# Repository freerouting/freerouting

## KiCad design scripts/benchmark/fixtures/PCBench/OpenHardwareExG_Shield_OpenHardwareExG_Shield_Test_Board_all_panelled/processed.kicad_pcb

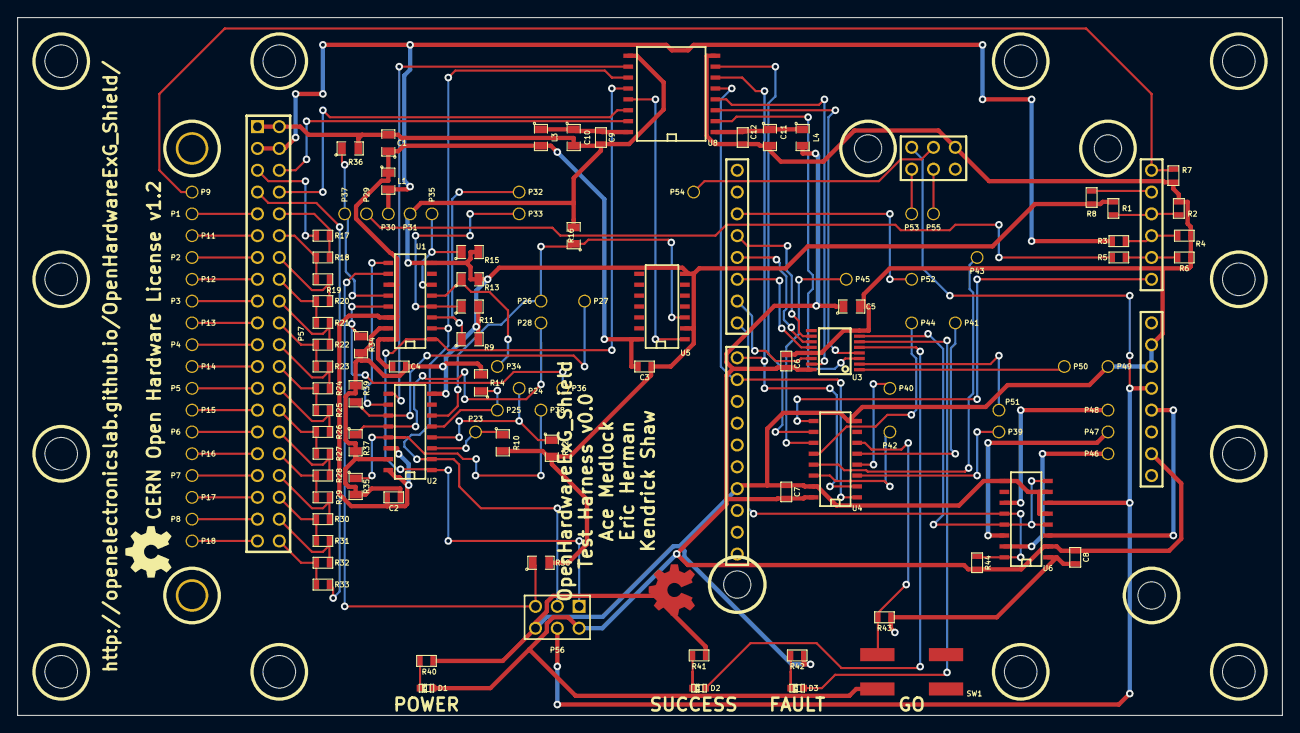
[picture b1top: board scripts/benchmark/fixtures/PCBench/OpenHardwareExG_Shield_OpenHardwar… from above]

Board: 4 copper layers, 147.3 x 81.3 mm, 137 parts (0 on the bottom side), 105 nets.

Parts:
C1, C5, C10, C11: 10uF; SM0805
C2, C3, C4, C6, C7, C8, C9, C12: 100nF; SM0603
D1, D2, D3: LED; LED-0603
Hole_M3, Hole_M3_2, Hole_M3_3, Hole_M3_4, Hole_M3_5, Hole_M3_6, Hole_M3_7, Hole_M3_8, Hole_M3_9, Hole_M3_10, Hole_M3_11, Hole_M3_12, Hole_M3_13, Hole_M3_14: VAL**; Hole_M3
L1, L3, L4: MH2029-221Y; SM0805
P1, P2, P3, P4, P5, P6, P7, P8, P9, P11, P12, P13, P14, P15, P16, P17, P18, P23, P24, P25, P26, P27, P28, P29, P30, P31, P32, P33, P34, P35, P36, P37, P38, P39, P40, P41, P42, P43, P44, P45, P46, P47, P48, P49, P50, P51, P52, P53, P54, P55: CONN_1; POGO_PIN_BASE
P19: ARDUINO_SHIELD; arduino_shield_with_holes
P56: CONN_3X2; pin_array_3x2
P57: CONN_20X2; PIN_ARRAY_20X2
R1, R3, R5, R43, R44: 10k; SM0603
R2, R4, R6: 1k; SM0603
R7: 5.1K; SM0603
R8, R18, R19, R20, R21, R22, R23, R24, R25, R26, R27, R28, R29, R30, R31, R32: 100; SM0603
R9, R10, R11, R12, R13, R14, R15, R16, R34, R35, R36, R37, R38, R39: 1M; SM0805
R17, R33: 15k; SM0603
R40, R41, R42: 560; SM0603
SW1: SW_PUSH; smt-tactile-button
U1, U2, U4: 74HC165; SO16E
U3: 74HC595PWR; TSSOP16
U5: 74LS125; SO14E
U6: TPS2095D; SO16E
U8: SI8661; SO16W

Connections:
+3.3V: P19.93, U6.3
+5V: P19.88, P19.94, P56.4, U6.6
/3.3V_BOGUS_ISO: L1.2, P30.1, P57.3, P57.4, R3.1
/3.3V_BOGUS_ISO_DATA: C9.1, C10.1, L3.1, U8.16
/A1: P19.55, R5.2, R6.1
/A2: P19.56, R3.2, R4.1
/A3: P19.57, R1.2, R2.1
/A4: P19.58, R8.2
/ADS129x_CLK_BOGUS_ISO: P38.1, R35.1, U2.13
/ADS129x_DAISY_IN_BOGUS_ISO: P36.1, R34.1, U1.13
/ADS129x_DOUT: P44.1, U4.12
/ADS129x_DOUT_BOGUS_ISO: P27.1, R39.1, U2.11
/ADS129x_GPIO1_BOGUS_ISO: P32.1, R9.1, U1.3
/ADS129x_GPIO2_BOGUS_ISO: P33.1, R11.1, U1.4
/ADS129x_GPIO3_BOGUS_ISO: P34.1, R13.1, U1.5
/ADS129x_GPIO4_BOGUS_ISO: P35.1, R15.1, U1.6
/ADS129x_MOSI_BOGUS_ISO: P23.1, R10.1, U2.3
/ADS129x_SCLK_BOGUS_ISO: P24.1, R12.1, U2.4
/ADS129x_~CS~: P42.1, U4.14
/ADS129x_~CS~_BOGUS_ISO: P25.1, R14.1, U2.5
/ADS129x_~DRDY~: P45.1, U4.11
/ADS129x_~DRDY~_BOGUS_ISO: P28.1, R37.1, U2.12
/ARDUINO_VCC: C5.1, C6.1, C7.1, C8.1, D1.1, L4.2, P19.91, P56.2, R44.2, SW1.2, U3.16, U4.16, U6.2
/BIASINV: P37.1, R36.1, U1.12
/BIASOUT_FILT: P9.1, P19.59, R7.1
/ENABLE_SHIELD: U3.7, U6.4, U6.8, U6.13
/FAULT_LED: D3.1, U3.6
/GO_BUTTON: R43.1, SW1.1, U4.6
/IN1N: P8.1, P57.37
/IN1N_LADDER: P57.38, R31.2, R32.2
/IN1P: P18.1, P57.39
/IN1P_LADDER: P57.40, R32.1, R33.1
/IN2N: P7.1, P57.33
/IN2N_LADDER: P57.34, R29.2, R30.2
/IN2P: P17.1, P57.35
/IN2P_LADDER: P57.36, R30.1, R31.1
/IN3N: P6.1, P57.29
/IN3N_LADDER: P57.30, R27.2, R28.2
/IN3P: P16.1, P57.31
/IN3P_LADDER: P57.32, R28.1, R29.1
/IN4N: P5.1, P57.25
/IN4N_LADDER: P57.26, R25.2, R26.2
/IN4P: P15.1, P57.27
/IN4P_LADDER: P57.28, R26.1, R27.1
/IN5N: P4.1, P57.21
/IN5N_LADDER: P57.22, R23.2, R24.2
/IN5P: P14.1, P57.23
/IN5P_LADDER: P57.24, R24.1, R25.1
/IN6N: P3.1, P57.17
/IN6N_LADDER: P57.18, R21.2, R22.2
/IN6P: P13.1, P57.19
/IN6P_LADDER: P57.20, R22.1, R23.1
/IN7N: P2.1, P57.13
/IN7N_LADDER: P57.14, R19.2, R20.2
/IN7P: P12.1, P57.15
/IN7P_LADDER: P57.16, R20.1, R21.1
/IN8N: P1.1, P57.9
/IN8N_LADDER: P57.10, R17.2, R18.2
/IN8P: P11.1, P57.11
/IN8P_LADDER: P57.12, R18.1, R19.1
/LED1: D1.2, R40.1
/LED2: D2.2, R41.1
/LED3: D3.2, R42.1
/MASTER: P43.1, U4.13
/MASTER_AND_MASTER_CS: P40.1, U4.4
/MASTER_BOGUS_ISO: P26.1, R16.1, U2.6, U5.3
/MASTER_~CS~: P50.1, U3.1
/MASTER_~DRDY~: P19.2, P52.1
/MIDDLE_CARRY: U1.9, U2.10
/MISO: P19.74, P53.1
/MOSI: P19.75, P54.1
/SCLK: P19.76, P55.1
/SHIELD_3.3V: P47.1, U6.14
/SHIELD_5V: P48.1, U6.11
/SHIELD_VCC: P46.1, U6.15
/SHIFT_CARRY: U4.10, U8.7
/SHIFT_CARRY_BOGUS_ISO: U2.9, U8.10
/SHIFT_CLK: P19.8, U4.2, U8.6
/SHIFT_CLK_BOGUS_ISO: P56.3, U1.2, U2.2, U8.11
/SHIFT_EXT_CARRY_BOGUS_ISO: P56.5, R38.1, U1.10
/SHIFT_IN: P19.54, U4.9
/SHIFT_OUT: P19.6, U3.14
/SHIFT_OUT_RCLK: P19.5, U3.12
/SHIFT_OUT_SRCLK: P19.4, U3.11
/SHIFT_OUT_~SRCLR~: P19.3, U3.10
/SHIFT_SH_~LD~: P19.9, U4.1, U8.5
/SHIFT_SH_~LD~_BOGUS_ISO: P56.1, U1.1, U2.1, U8.12
/SIGNAL_A: U3.3, U8.2
/SIGNAL_A_BOGUS_ISO: P57.6, U8.15
/SIGNAL_A_LADDER: P57.5, R17.1
/SIGNAL_B: U3.4, U8.3
/SIGNAL_B_BOGUS_ISO: P57.8, U8.14
/SIGNAL_B_LADDER: P57.7, R33.2
/SLAVE_AND_SLAVE_CS: P39.1, U4.3
/SLAVE_~CS~: P51.1, U3.2
/SUCCESS_LED: D2.1, U3.5
/VCC_DATA: C11.1, C12.1, L4.1, U8.1
/VIN_BOGUS_ISO: P29.1, R5.1
/~MASTER~: P41.1, U4.5
/~SEND_TO_GND~_MASTER: U3.15, U8.4
/~SEND_TO_GND~_MASTER_BOGUS_ISO: U5.1, U8.13
/~SHIELD_SHORTED~: P19.7, R44.1, U6.12, U6.16
GND: C1.2, C2.2, C3.2, C4.2, C9.2, C10.2, P31.1, P57.1, P57.2, R1.1, R8.1, R9.2, R10.2, R11.2, R12.2, R13.2, R14.2, R15.2, R16.2, R34.2, R35.2, R36.2, R37.2, R38.2, R39.2, U1.8, U1.15, U2.8, U2.15, U5.2, U5.7, U8.9
GNDPWR: C5.2, C6.2, C7.2, C8.2, C11.2, C12.2, P19.87, P19.95, P19.96, P19.99, P49.1, P56.6, R2.2, R4.2, R6.2, R7.2, R40.2, R41.2, R42.2, R43.2, U3.8, U3.13, U4.8, U4.15, U6.1, U6.5, U6.7, U6.9, U8.8
VCC: C1.1, C2.1, C3.1, C4.1, L1.1, L3.2, U1.11, U1.14, U1.16, U2.14, U2.16, U5.14

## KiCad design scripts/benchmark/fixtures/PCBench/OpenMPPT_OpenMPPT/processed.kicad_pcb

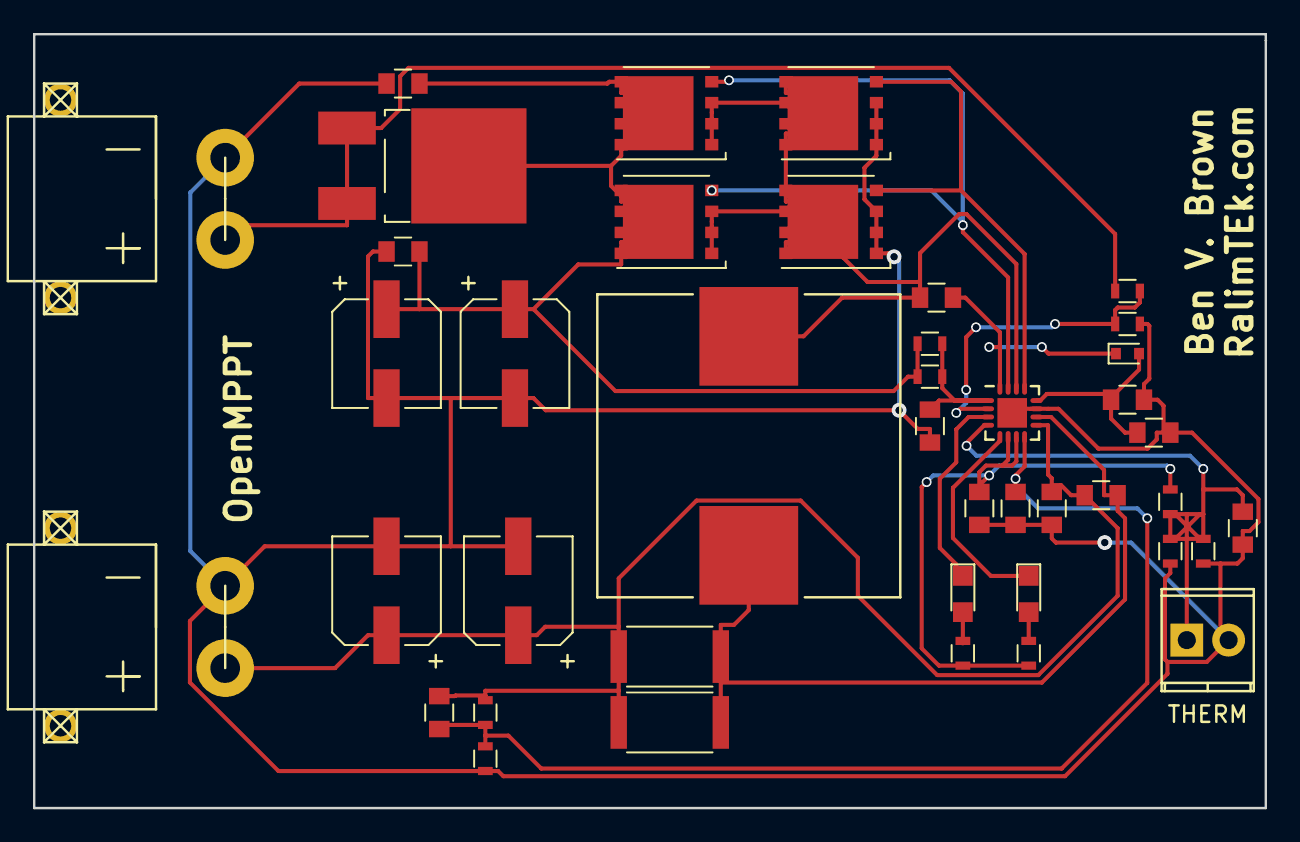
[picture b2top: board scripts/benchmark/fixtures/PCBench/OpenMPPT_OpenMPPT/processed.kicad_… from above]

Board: 2 copper layers, 74.8 x 47.0 mm, 42 parts (0 on the bottom side), 19 nets.

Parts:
C101: -; C_0805
C102, C103, C106, C107, C110, C115: 1.0uF; C_0805
C104, C105, C109, C112, C113: 0.1uF; C_0805
C108, C111, C114, C116: CP; CP_Elec_6.3x7.7
D101: MBRD10100CT; TO-252-2_Rectifier
D102: D_Schottky; D_SOD-523
D103, D104: LED; LED_0805
J101: THERM; TerminalBlock_Pheonix_MPT-2.54mm_2pol
J103, J104: XT60; XT30PW_Male
L101: 3.3uH; Inductor_Wurth_HCI-1890
Q101, Q102, Q103, Q104: FDMS8050; TDSON-8-1
R101: 10k; R_0603
R102, R108, R109: 5.23k; R_0603
R103: 30.1k; R_0603
R105: -; R_0603
R106: 10; R_0603
R110, R113: 0.01; R_2512
R111, R114: 499k; R_0603
R112: 100k; R_0603
R115: 36k; R_0603
U101: BQ24650; QFN-16-1EP_3x3mm_Pitch0.5mm

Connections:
/HIGH_DRIVE: Q101.4, Q103.4, U101.15
/LOW_DRIVE: Q102.4, Q104.4, U101.13
/MPPTSET: R114.2, R115.1, U101.2
/STAT1: D103.1, U101.3
/STAT2: D104.1, U101.5
/VREF: C103.1, R102.1, R108.1, R109.1, U101.6, U101.7
GND: C101.2, C102.1, C103.2, C104.2, C106.2, C107.2, C108.2, C110.2, C111.2, C113.1, C114.2, C115.2, C116.2, J101.2, J103.2, J104.2, Q102.1, Q102.2, Q102.3, Q104.1, Q104.2, Q104.3, R101.2, R103.2, R112.2, R115.2, U101.11, U101.17
unnamed: C101.1, J101.1, R101.1, R102.2, R103.1, U101.4
unnamed: C102.2, R105.2, R106.2, U101.1
unnamed: C104.1, C107.1, D102.2, U101.12
unnamed: C105.1, L101.1, Q101.1, Q101.2, Q101.3, Q102.5, Q103.1, Q103.2, Q103.3, Q104.5, U101.14
unnamed: C105.2, D102.1, U101.16
unnamed: C106.1, C108.1, C114.1, C115.1, D101.2, Q101.5, Q103.5, R105.1, R106.1
unnamed: C109.1, C110.1, C111.1, C112.2, C116.1, J104.1, R110.1, R111.1, R113.2, U101.9
unnamed: C109.2, L101.2, R110.2, R113.1, U101.10
unnamed: C112.1, C113.2, R111.2, R112.1, U101.8
unnamed: D101.1, D101.3, J103.1, R114.1
unnamed: D103.2, R108.2
unnamed: D104.2, R109.2

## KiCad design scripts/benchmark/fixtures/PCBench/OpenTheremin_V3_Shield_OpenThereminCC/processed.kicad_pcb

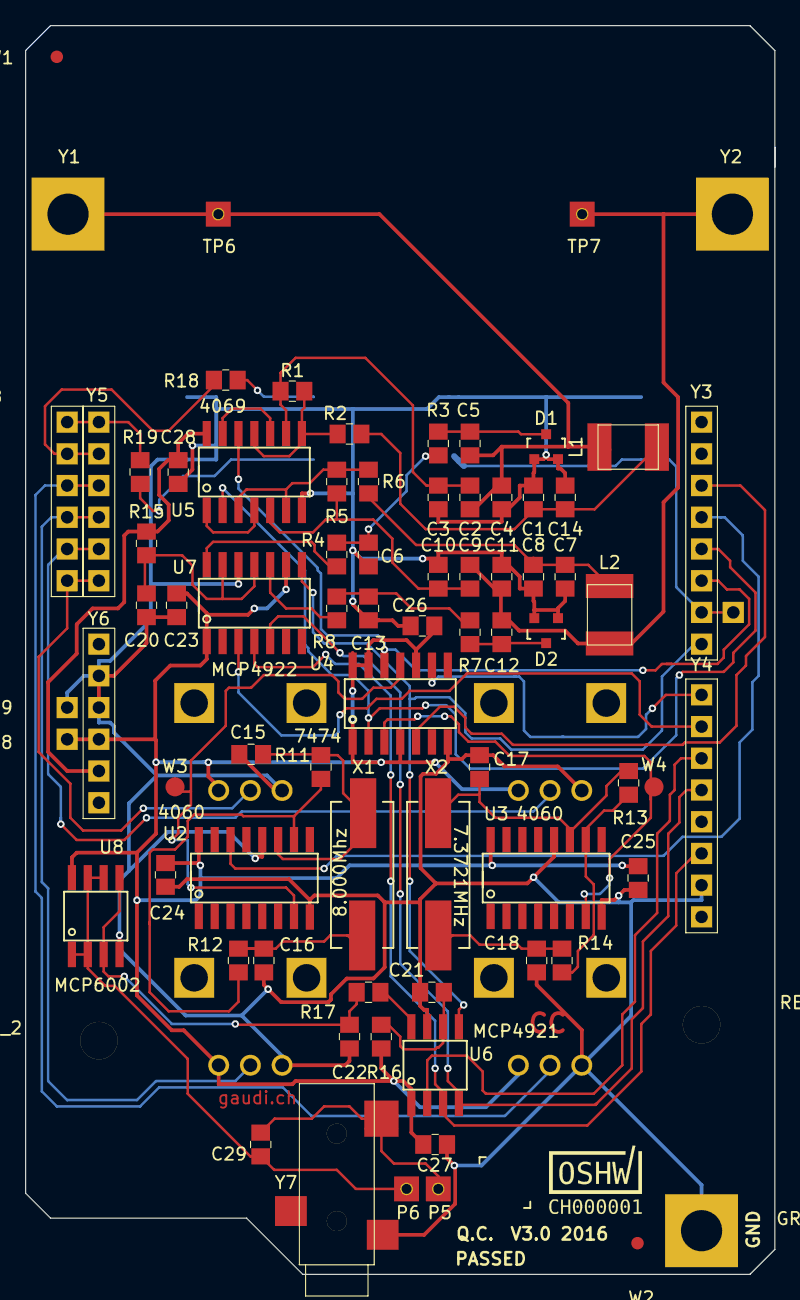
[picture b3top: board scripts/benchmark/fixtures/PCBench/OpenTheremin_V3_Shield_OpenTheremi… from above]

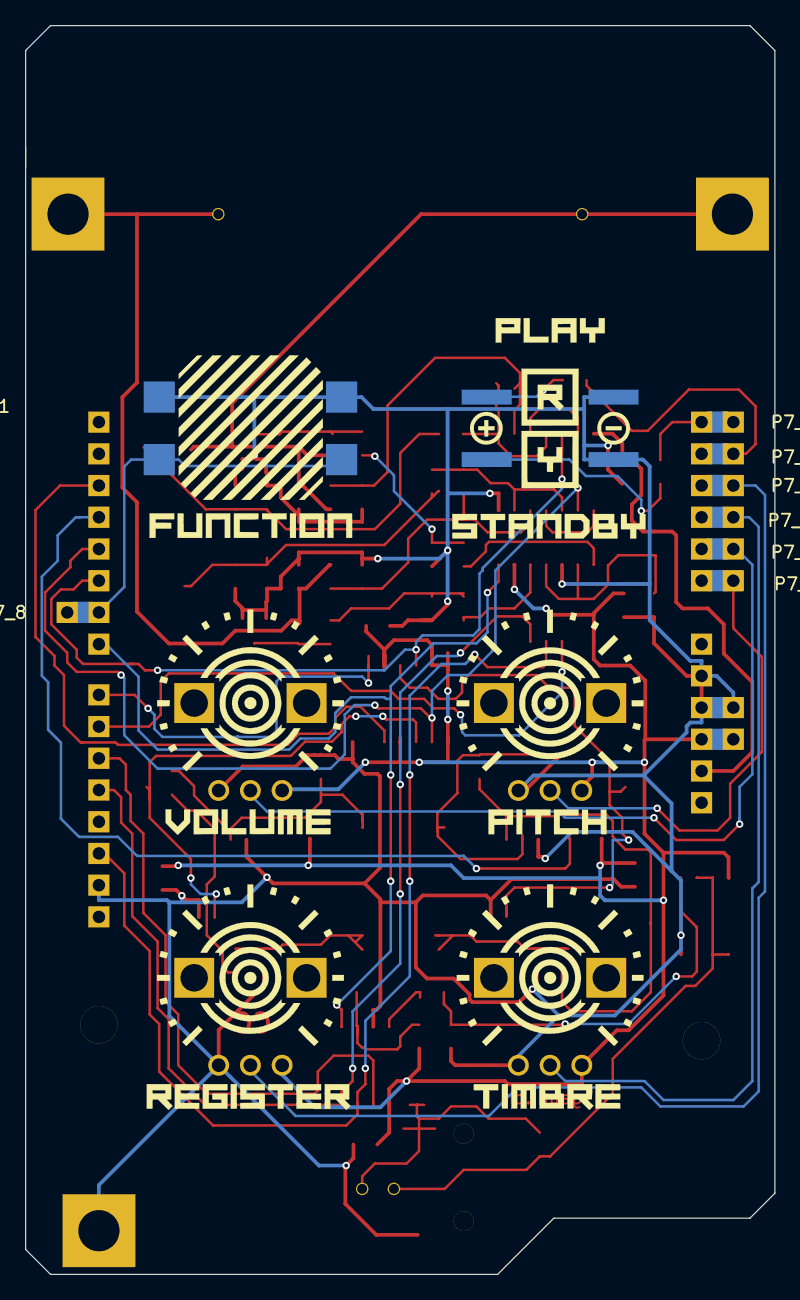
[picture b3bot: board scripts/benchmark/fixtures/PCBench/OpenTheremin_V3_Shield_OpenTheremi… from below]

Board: 2 copper layers, 60.0 x 100.0 mm, 95 parts (17 on the bottom side), 52 nets.

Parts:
C1: 220pF 270pF?; 0805G
C2, C3, C9, C10: 150pF; 0805G
C4: 15nF?; 0805G
C5, C12: 470pF; 0805G
C6, C13, C23, C24, C25, C26, C27, C28: 100nF; 0805G
C7, C14: ?pF; 0805G
C8: 330pF; 0805G
C11: 0; 0805G
C15, C16, C17, C18: 33pF; 0805G
C20, C21: 100n; 0805G
C22: 10n; 0805G
C29: 10uF; 0805G
D1, D2: BB914; SOT-23
D3, D4: LED; LED_SQUARE_5mm
GROUND1: GND_PAD; MountPad3
L1, L2: 1mH; COIL
P1, P2, P3, P4: 10k; POT
P5: SP+; MeasurePad_Square_wHole_2mm
P6: SP-; MeasurePad_Square_wHole_2mm
P7, P7_2, P7_3, P7_4, P7_5, P7_6, P7_7, P7_8, P7_10: CONN_01X01; SMD_Pinheader_1_OT_BLANK
P7_9, P8, P9: CONN_01X01; SMD_Pinheader_1_OT
R1, R5, R11, R13: 4.7M; 0805G
R2, R6, R17: 2.2k; 0805G
R3, R4, R7, R8, R15, R16: 100k; 0805G
R12, R14, R18, R19: 470; 0805G
SW1: SW_PUSH; PUSH_BUTTON_TL3300D
TP6: PITCH ANTENNA; MeasurePad_Square_wHole_2mm
TP7: VOLUME ANTENNA; MeasurePad_Square_wHole_2mm
U1: Arduino_UNO_R2; ArduinoUNO
U2, U3: 4060; SOIC-16_N
U4: 74HC74; SOIC-14_N
U5: 4069; SOIC-14_N
U6: MCP4921-E/SN; SOIC-08_N
U7: MCP4922-E/SL; SOIC-14_N
U8: LM358 / MCP6002; SOIC-08_N
W1: FIDUCIAL1; Fiducial_1mm_Dia_2.54mm_Outer_CopperTop
W2: FIDUCIAL2; Fiducial_1mm_Dia_2.54mm_Outer_CopperTop
W3: TP1; Measurement_Point_Round-SMD-Pad_Small
W4: TP2; Measurement_Point_Round-SMD-Pad_Small
X1: 8MHz; Crystal_HC49-SD_SMD
X2: 7.3721MHz; Crystal_HC49-SD_SMD
Y1, Y2: MountPad3
Y3, Y4: CONN_01X08; SMD_Pinheader_8_OT
Y5, Y6, Y8: CONN_01X06; SMD_Pinheader_6_OT
Y7: PLUG_3_5_SMD; PLUG3_5_SwitchCraft_2B

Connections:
A0: P1.2, Y5.6, Y8.6
A1: P2.2, Y5.5, Y8.5
A2: P3.2, Y5.4, Y8.4
A3: P4.2, Y5.3, Y8.3
BUT: P7_9.1, SW1.1, Y3.7
DAC2_CS: U7.3, Y4.2
DAC_CS: U6.2, Y4.3
DAC_DI: U6.4, U7.5, Y4.4
DAC_LATCH: U6.5, U7.8, Y3.8
DAC_SCK: U6.3, U7.4, Y4.6
F_PITCH: U4.9, Y4.1
F_VOL: U4.5, Y3.3
GND: C1.2, C3.2, C4.2, C6.2, C7.2, C8.2, C10.2, C11.2, C13.2, C14.2, C15.2, C16.2, C17.2, C18.2, C20.2, C21.2, C22.2, C23.2, C24.2, C25.2, C26.2, C27.2, C28.2, D1.1, D1.2, D2.1, D2.2, D3.1, D4.1, GROUND1.1, P1.1, P2.1, P3.1, P4.1, P9.1, SW1.2, U2.8, U2.12, U3.8, U3.12, U4.7, U5.7, U6.7, U7.12, U8.4, Y4.7, Y6.2, Y6.3, Y7.1
LED_GREEN: R18.2, Y5.2, Y8.2
LED_RED: R19.2, Y5.1, Y8.1
unnamed: C1.1, C14.1, L1.2, R2.1
unnamed: C2.1, C4.1, C5.1, L1.1, TP6.1, Y1.1
unnamed: C2.2, C3.1, R1.2, U5.9
unnamed: C5.2, D1.3, R3.2
unnamed: C6.1, R3.1, R4.1
unnamed: C7.1, C8.1, L2.2, R6.1
unnamed: C9.2, C10.1, R5.2, U5.5
unnamed: C9.1, C11.1, C12.1, L2.1, TP7.1, Y2.1
unnamed: C12.2, D2.3, R7.2
unnamed: C13.1, R7.1, R8.1
unnamed: C15.1, R11.2, U2.11, X1.1
unnamed: C16.1, R12.1, X1.2
unnamed: C17.1, R13.2, U3.11, X2.1
unnamed: C18.1, R14.1, X2.2
unnamed: C21.1, R16.1, U6.6
unnamed: C22.1, R17.2, U8.3, U8.5
unnamed: C29.1, P6.1, U8.1, U8.2, U8.6, U8.7
unnamed: C29.2, P5.1, Y7.3
unnamed: D3.2, R18.1
unnamed: D4.2, R19.1
unnamed: R1.1, R2.2, U5.8, U5.11
unnamed: R4.2, U7.14
unnamed: R5.1, R6.2, U5.3, U5.6
unnamed: R11.1, R12.2, U2.10
unnamed: R13.1, R14.2, U3.10
unnamed: R17.1, U6.8
unnamed: U2.7, U4.11, W3.1
unnamed: U3.7, U4.3, W4.1
unnamed: U5.1, U5.4
unnamed: U5.10, U5.13
SAMPLE_CLK: U2.14, Y3.4
VCC: C23.1, C24.1, C25.1, C26.1, C27.1, P1.3, P2.3, P3.3, P4.3, P8.1, R16.2, U2.16, U3.16, U4.1, U4.4, U4.10, U4.13, U4.14, U6.1, U7.1, U7.9, U8.8, Y6.4
VDD: C28.1, R15.2, U5.14, Y6.5
VO_PITCH: U4.12, U5.12, Y3.6
VO_VOL: U4.2, U5.2, Y3.5
VoutB: R8.2, U7.10
VrefB: C20.1, R15.1, U7.11, U7.13

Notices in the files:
scripts/benchmark/fixtures/PCBench/OpenHardwareExG_Shield_OpenHardwareExG_Shield_Test_Board_all_panelled/processed.kicad_pcb:
CERN Open Hardware License v1.2
